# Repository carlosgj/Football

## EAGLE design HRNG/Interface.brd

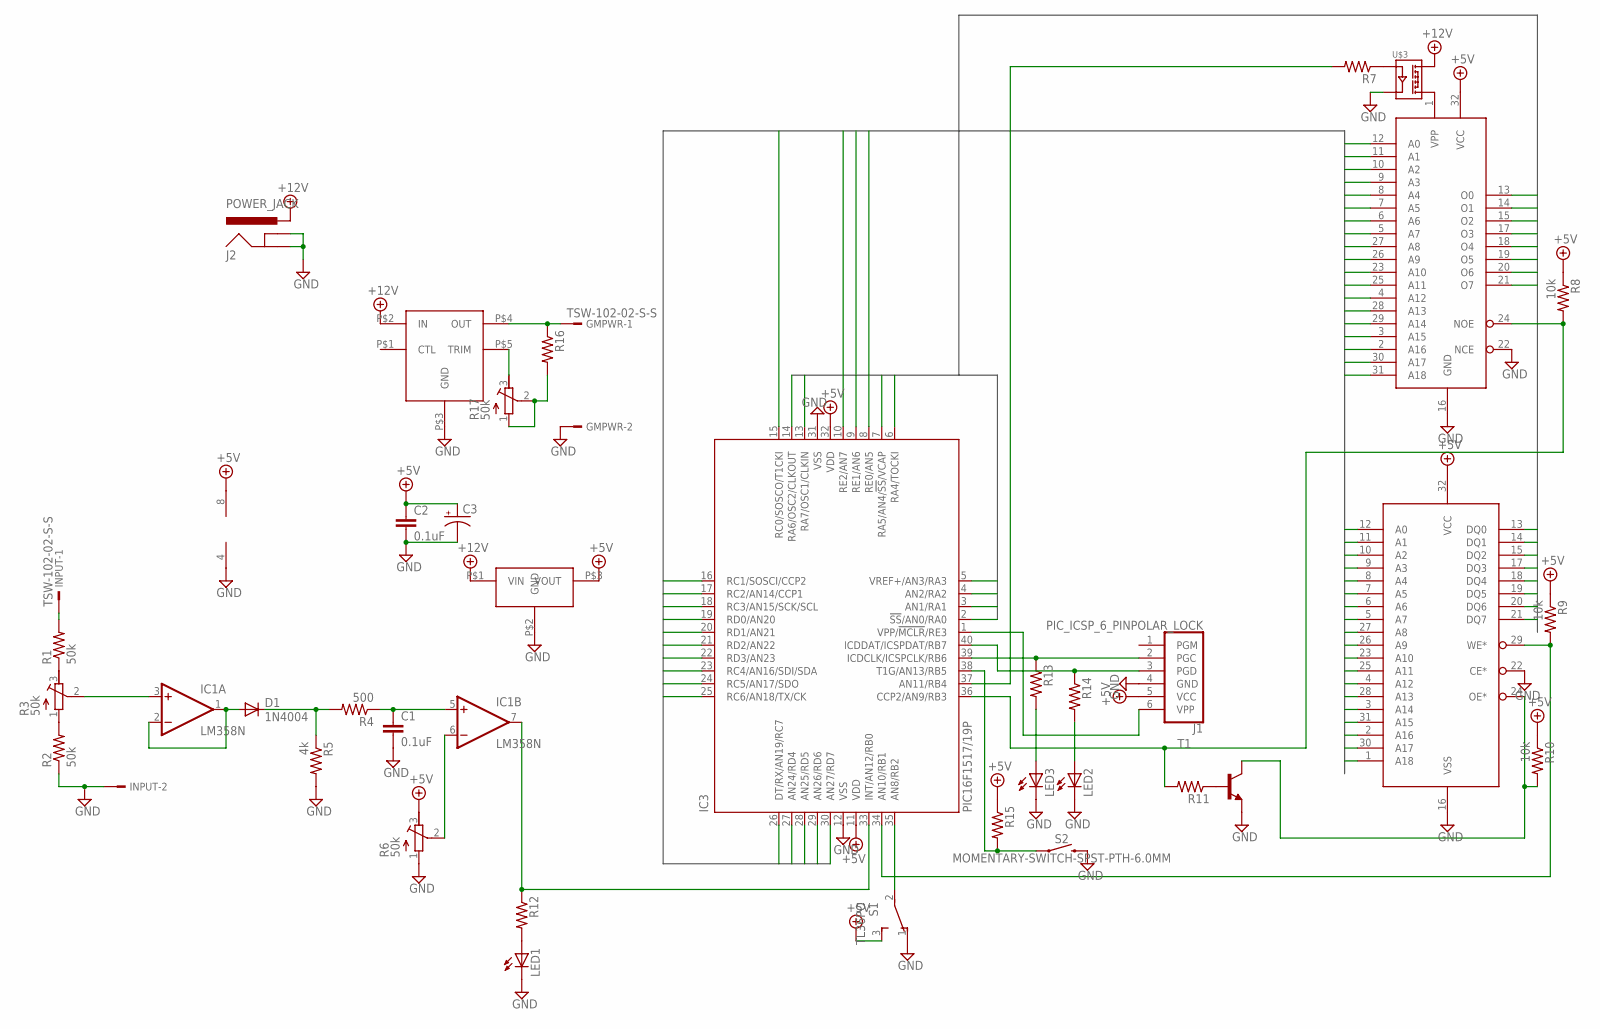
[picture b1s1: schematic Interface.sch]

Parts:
C1, C2: 0.1uF; C050-025X075
C3: CPOL-USE5-8.5; E5-8,5
D1: 1N4004; DO41-10
GMPWR: TSW-102-02-S-S
IC1: LM358N; DIL08
IC3: PIC16F1517/19P; DIL40
INPUT: TSW-102-02-S-S
J1: PIC_ICSP_6_PINPOLAR_LOCK; MOLEX-1X6_LOCK
J2: POWER_JACK; POWER_JACK_PTH
LED1, LED2, LED3: LED3MM
R1, R2: 50k; 0204V
R3, R6, R17: 50k; RTRIM3296W
R4: 500; 0204V
R5: 4k; 0204V
R7, R11, R12, R13, R14, R15, R16: R-US_0204/2V; 0204V
R8, R9, R10: 10k; 0204V
S1: TL36PO; TL3XPO
S2: MOMENTARY-SWITCH-SPST-PTH-6.0MM; TACTILE_SWITCH_PTH_6.0MM
T1: MPS2222A-NPN-TO92-CBE; TO92-CBE
U$1: AT27C040; DIL32
U$2: AS6C4008; DIL32
U$3: CPC1008N; SOP04
U$4: OKR-T/1.5-W12-C; SIP5
U$5: OKI-78SR-5/1.5-W36-C; SIP_PS

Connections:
+5V: C2.1, C3.+, IC1.8 (V+), IC3.11 (VDD), IC3.32 (VDD), J1.5 (VCC), R6.3 (E), R8.1, R9.1, R10.1, R15.1, S1.3 (S), U$1.32 (VCC), U$2.32 (VCC), U$5.P$3 (VOUT)
+12V: J2.PWR, U$3.4 (DC), U$4.P$2 (IN), U$5.P$1 (VIN)
A0: IC3.15 (RC0/SOSCO/T1CKI), U$1.12 (A0), U$2.12 (A0)
A1: IC3.16 (RC1/SOSCI/CCP2), U$1.11 (A1), U$2.11 (A1)
A2: IC3.17 (RC2/AN14/CCP1), U$1.10 (A2), U$2.10 (A2)
A3: IC3.18 (RC3/AN15/SCK/SCL), U$1.9 (A3), U$2.9 (A3)
A4: IC3.23 (RC4/AN16/SDI/SDA), U$1.8 (A4), U$2.8 (A4)
A5: IC3.24 (RC5/AN17/SDO), U$1.7 (A5), U$2.7 (A5)
A6: IC3.25 (RC6/AN18/TX/CK), U$1.6 (A6), U$2.6 (A6)
A7: IC3.26 (DT/RX/AN19/RC7), U$1.5 (A7), U$2.5 (A7)
A8: IC3.19 (RD0/AN20), U$1.27 (A8), U$2.27 (A8)
A9: IC3.20 (RD1/AN21), U$1.26 (A9), U$2.26 (A9)
A10: IC3.21 (RD2/AN22), U$1.23 (A10), U$2.23 (A10)
A11: IC3.22 (RD3/AN23), U$1.25 (A11), U$2.25 (A11)
A12: IC3.27 (AN24/RD4), U$1.4 (A12), U$2.4 (A12)
A13: IC3.28 (AN25/RD5), U$1.28 (A13), U$2.28 (A13)
A14: IC3.29 (AN26/RD6), U$1.29 (A14), U$2.3 (A14)
A15: IC3.30 (AN27/RD7), U$1.3 (A15), U$2.31 (A15)
A16: IC3.8 (RE0/AN5), U$1.2 (A16), U$2.2 (A16)
A17: IC3.9 (RE1/AN6), U$1.30 (A17), U$2.30 (A17)
A18: IC3.10 (RE2/AN7), U$1.31 (A18), U$2.1 (A18)
D0: IC3.2 (!SS!/AN0/RA0), U$1.13 (O0), U$2.13 (DQ0)
D1: IC3.3 (AN1/RA1), U$1.14 (O1), U$2.14 (DQ1)
D2: IC3.4 (AN2/RA2), U$1.15 (O2), U$2.15 (DQ2)
D3: IC3.5 (VREF+/AN3/RA3), U$1.17 (O3), U$2.17 (DQ3)
D4: IC3.6 (RA4/TOCKI), U$1.18 (O4), U$2.18 (DQ4)
D5: IC3.7 (RA5/AN4/!SS!/VCAP), U$1.19 (O5), U$2.19 (DQ5)
D6: IC3.14 (RA6/OSC2/CLKOUT), U$1.20 (O6), U$2.20 (DQ6)
D7: IC3.13 (RA7/OSC1/CLKIN), U$1.21 (O7), U$2.21 (DQ7)
GND: C1.2, C2.2, C3.-, GMPWR.2, IC1.4 (V-), IC3.12 (VSS), IC3.31 (VSS), INPUT.2, J1.4 (GND), J2.GND, J2.GNDBREAK, LED1.K (C), LED2.K (C), LED3.K (C), R2.1, R5.2, R6.1 (A), S1.1 (O), S2.3 (2), T1.E, U$1.16 (GND), U$1.22 (NCE), U$2.16 (VSS), U$2.22 (CE*), U$3.3 (IN-), U$4.P$3 (GND), U$5.P$2 (GND)
unnamed: R1.1, R3.3 (E)
unnamed: R2.2, R3.1 (A)
unnamed: IC1.6 (-IN), R6.2 (S)
unnamed: INPUT.1, R1.2
unnamed: D1.A, IC1.1 (OUT), IC1.2 (-IN)
unnamed: IC1.3 (+IN), R3.2 (S)
unnamed: D1.C, R4.2, R5.1
unnamed: C1.1, IC1.5 (+IN), R4.1
unnamed: IC3.39 (ICDCLK/ICSPCLK/RB6), J1.2 (PGC), R13.1
unnamed: IC3.40 (ICDDAT/ICSPDAT/RB7), J1.3 (PGD), R14.1
unnamed: IC3.34 (AN10/RB1), R9.2, U$2.29 (WE*)
unnamed: R11.1, T1.B
unnamed: IC3.36 (CCP2/AN9/RB3), R8.2, R11.2, U$1.24 (NOE)
unnamed: IC1.7 (OUT), IC3.33 (INT/AN12/RB0), R12.1
unnamed: IC3.1 (VPP/!MCLR!/RE3), J1.6 (VPP)
unnamed: U$1.1 (VPP), U$3.6 (DC)
unnamed: R7.1, U$3.1 (IN+)
unnamed: IC3.37 (AN11/RB4), R7.2
unnamed: R10.2, T1.C, U$2.24 (OE*)
unnamed: LED1.A, R12.2
unnamed: IC3.35 (AN8/RB2), S1.2
unnamed: LED2.A, R14.2
unnamed: LED3.A, R13.2
unnamed: IC3.38 (T1G/AN13/RB5), R15.2, S2.1
unnamed: GMPWR.1, R16.1, U$4.P$4 (OUT)
unnamed: R17.3 (E), U$4.P$5 (TRIM)
unnamed: R16.2, R17.1 (A), R17.2 (S)

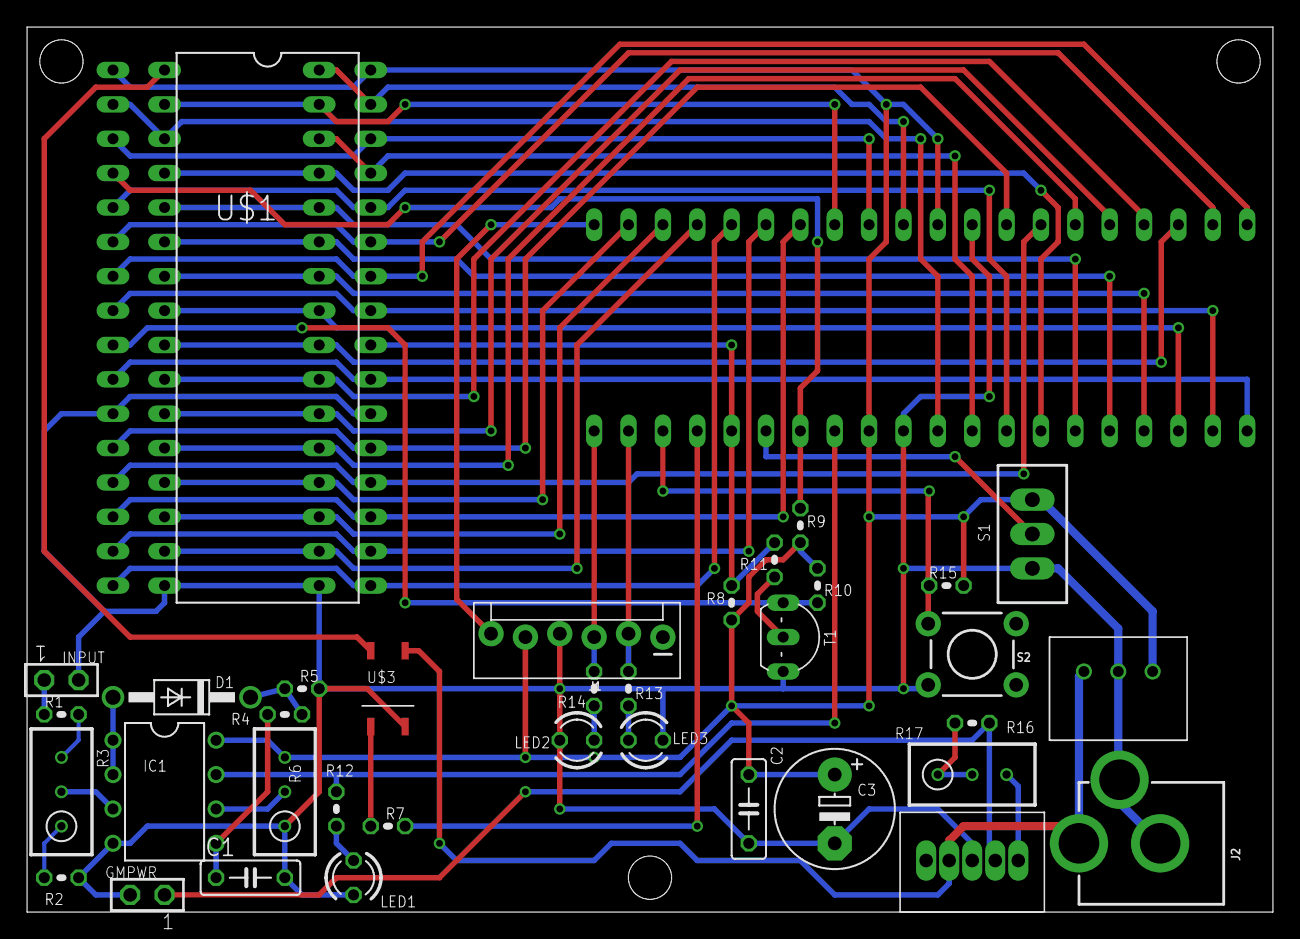
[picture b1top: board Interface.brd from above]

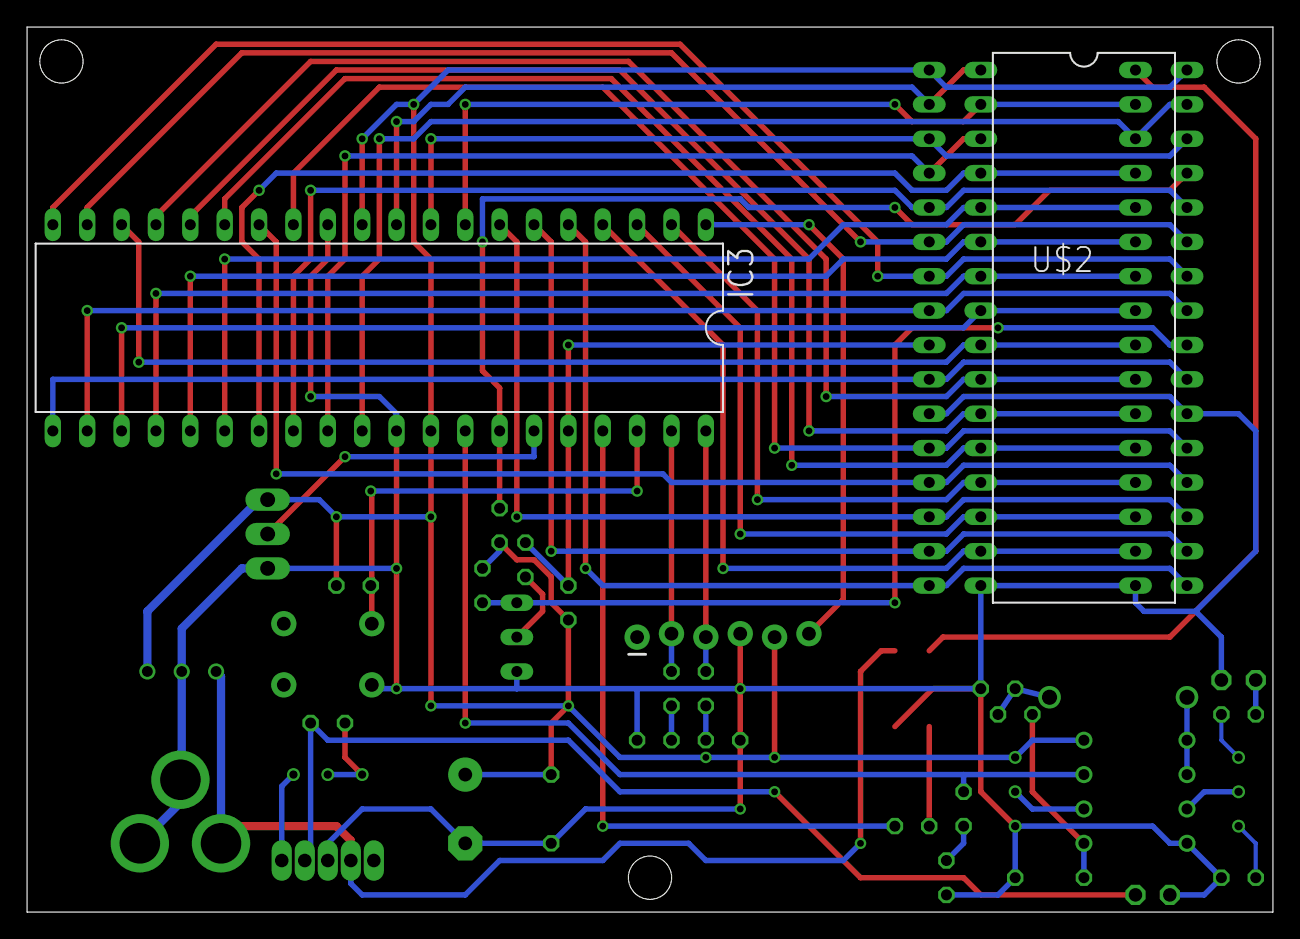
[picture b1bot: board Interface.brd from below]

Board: 2 copper layers, 92.1 x 65.4 mm, 38 parts (2 on the bottom side), 57 nets.

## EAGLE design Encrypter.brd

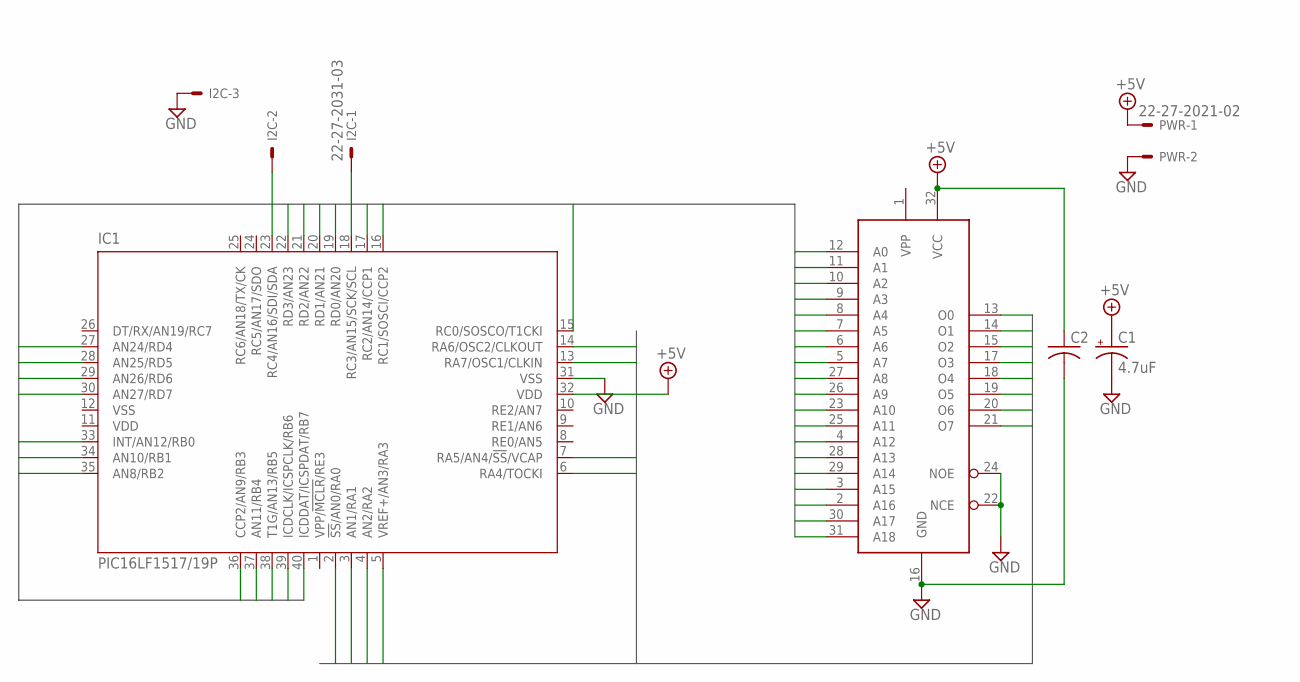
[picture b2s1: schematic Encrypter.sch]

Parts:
C1: 4.7uF; E3,5-10
C2: C-US050-025X075; C050-025X075
I2C: 22-27-2031-03; 6410-03
IC1: PIC16LF1517/19P; DIL40
PWR: 22-27-2021-02; 6410-02
U$1: AT27C040; DIL32

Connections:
+5V: C1.+, C2.1, IC1.32 (VDD), PWR.1, U$1.32 (VCC)
A0: IC1.33 (INT/AN12/RB0), U$1.12 (A0)
A1: IC1.34 (AN10/RB1), U$1.11 (A1)
A2: IC1.35 (AN8/RB2), U$1.10 (A2)
A3: IC1.36 (CCP2/AN9/RB3), U$1.9 (A3)
A4: IC1.37 (AN11/RB4), U$1.8 (A4)
A5: IC1.38 (T1G/AN13/RB5), U$1.7 (A5)
A6: IC1.39 (ICDCLK/ICSPCLK/RB6), U$1.6 (A6)
A7: IC1.40 (ICDDAT/ICSPDAT/RB7), U$1.5 (A7)
A8: IC1.15 (RC0/SOSCO/T1CKI), U$1.27 (A8)
A9: IC1.16 (RC1/SOSCI/CCP2), U$1.26 (A9)
A10: IC1.17 (RC2/AN14/CCP1), U$1.23 (A10)
A11: IC1.19 (RD0/AN20), U$1.25 (A11)
A12: IC1.20 (RD1/AN21), U$1.4 (A12)
A13: IC1.21 (RD2/AN22), U$1.28 (A13)
A14: IC1.22 (RD3/AN23), U$1.29 (A14)
A15: IC1.27 (AN24/RD4), U$1.3 (A15)
A16: IC1.28 (AN25/RD5), U$1.2 (A16)
A17: IC1.29 (AN26/RD6), U$1.30 (A17)
A18: IC1.30 (AN27/RD7), U$1.31 (A18)
GND: C1.-, C2.2, I2C.3, IC1.31 (VSS), PWR.2, U$1.16 (GND), U$1.22 (NCE), U$1.24 (NOE)
unnamed: I2C.1, IC1.18 (RC3/AN15/SCK/SCL)
unnamed: I2C.2, IC1.23 (RC4/AN16/SDI/SDA)
O0: IC1.2 (!SS!/AN0/RA0), U$1.13 (O0)
O1: IC1.3 (AN1/RA1), U$1.14 (O1)
O2: IC1.4 (AN2/RA2), U$1.15 (O2)
O3: IC1.5 (VREF+/AN3/RA3), U$1.17 (O3)
O4: IC1.6 (RA4/TOCKI), U$1.18 (O4)
O5: IC1.7 (RA5/AN4/!SS!/VCAP), U$1.19 (O5)
O6: IC1.14 (RA6/OSC2/CLKOUT), U$1.20 (O6)
O7: IC1.13 (RA7/OSC1/CLKIN), U$1.21 (O7)
VDD: IC1.11 (VDD)
VSS: IC1.12 (VSS)

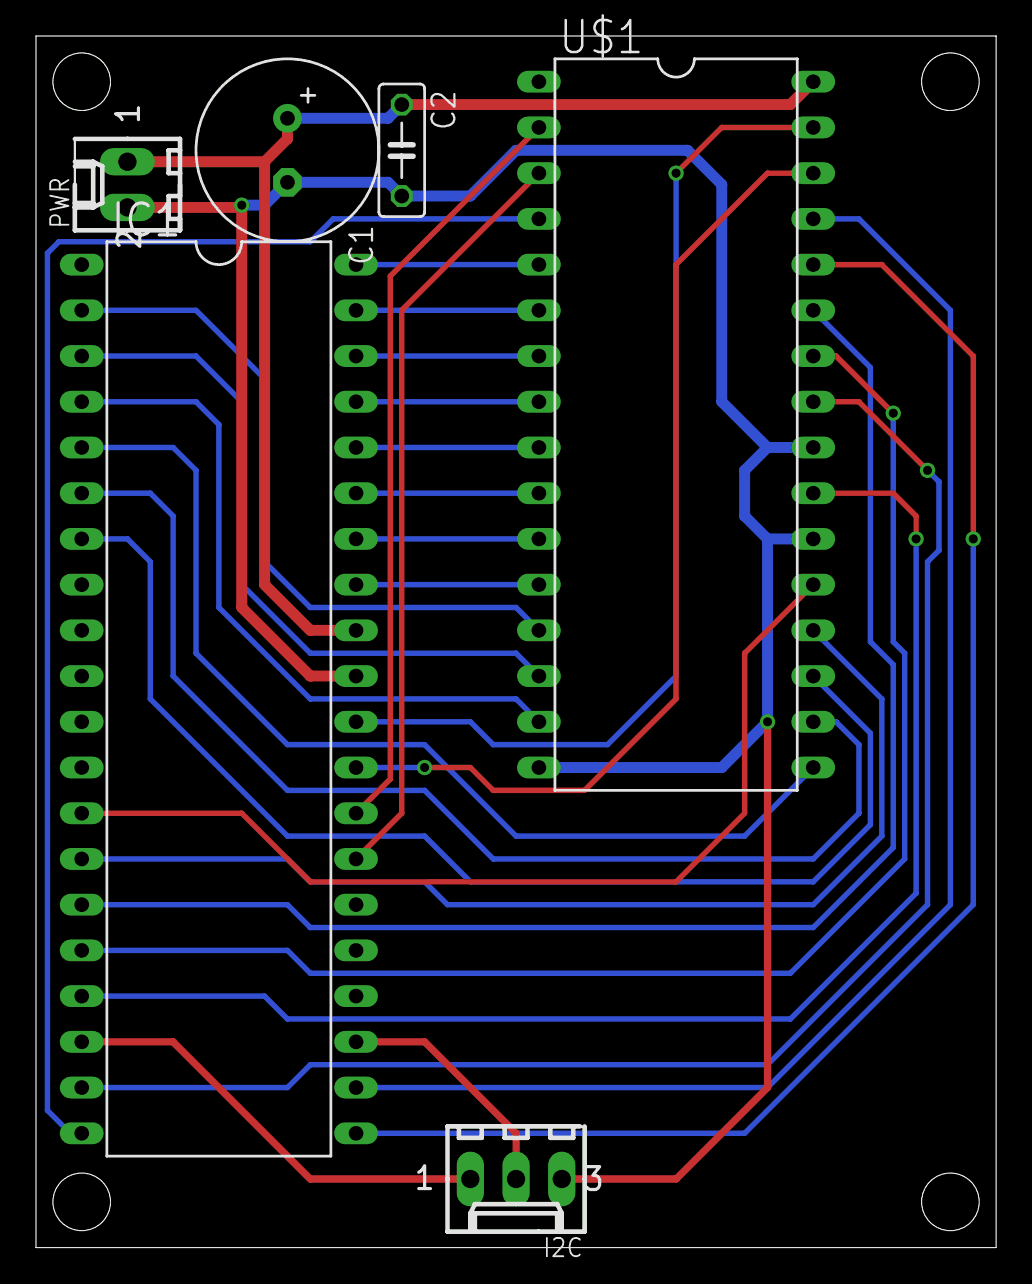
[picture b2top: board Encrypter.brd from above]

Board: 2 copper layers, 53.3 x 67.3 mm, 6 parts (0 on the bottom side), 31 nets.

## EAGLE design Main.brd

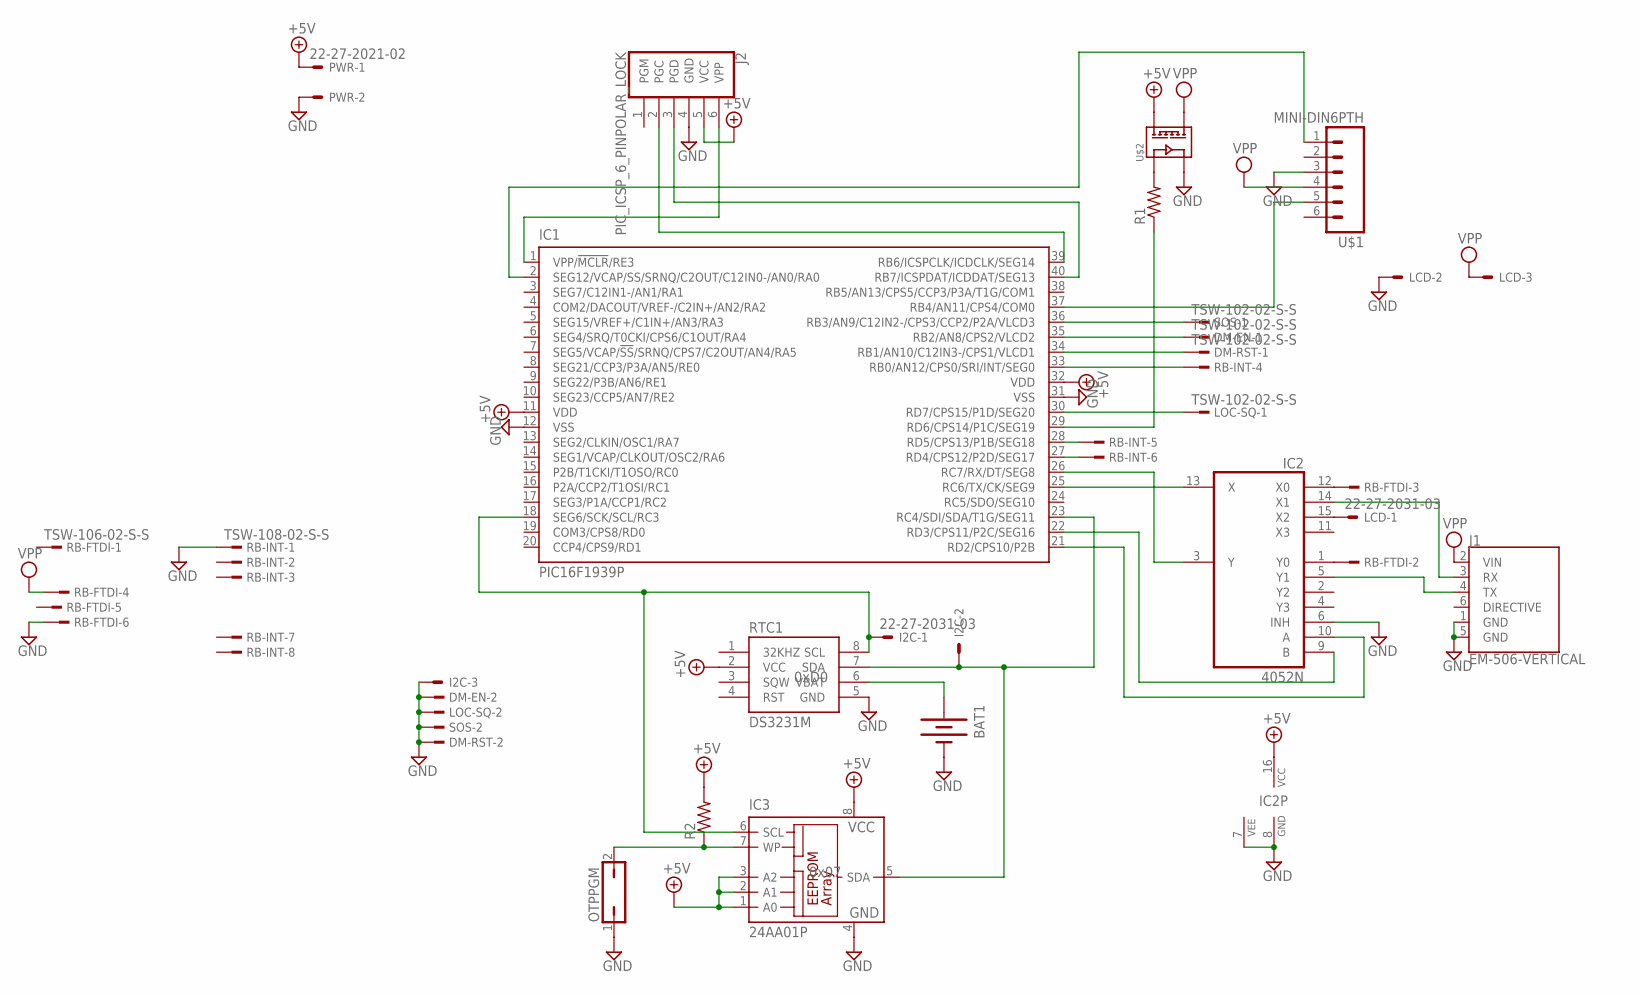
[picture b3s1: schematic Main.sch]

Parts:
BAT1: BATTERY12PTH; BATTCON_12MM_PTH
DM-EN: TSW-102-02-S-S
DM-RST: TSW-102-02-S-S
I2C: 22-27-2031-03; 6410-03
IC1: PIC16F1939P; DIL40
IC2: 4052N; DIL16
IC3: 24AA01P; DIL8
J1: EM-506-VERTICAL; EM406
J2: PIC_ICSP_6_PINPOLAR_LOCK; MOLEX-1X6_LOCK
LCD: 22-27-2031-03; 6410-03
LOC-SQ: TSW-102-02-S-S
OTPPGM: JP1Q; JP1
PWR: 22-27-2021-02; 6410-02
R1, R2: R-US_0204/2V; 0204V
RB-FTDI: TSW-106-02-S-S
RB-INT: TSW-108-02-S-S
RTC1: DS3231M; SOIC8
SOS: TSW-102-02-S-S
U$1: MINI-DIN6PTH; MINI-DIN6
U$2: CPC1008N; SOP04

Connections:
+5V: IC1.11 (VDD), IC1.32 (VDD), IC2.16 (VCC), IC3.1 (A0), IC3.2 (A1), IC3.3 (A2), IC3.8 (VCC), J2.5 (VCC), PWR.1, R2.2, RTC1.2 (VCC), U$2.4 (DC)
GND: BAT1.GND (-), DM-EN.2, DM-RST.2, I2C.3, IC1.12 (VSS), IC1.31 (VSS), IC2.6 (INH), IC2.7 (VEE), IC2.8 (GND), IC3.4 (GND), J1.1 (GND), J1.5 (GND), J2.4 (GND), LCD.2, LOC-SQ.2, OTPPGM.1, PWR.2, RB-FTDI.6, RB-INT.1, RTC1.5 (GND), SOS.2, U$1.3, U$2.3 (IN-)
unnamed: IC1.26 (RC7/RX/DT/SEG8), IC2.3 (Y)
unnamed: IC1.25 (RC6/TX/CK/SEG9), IC2.13 (X)
unnamed: I2C.1, IC1.18 (SEG6/SCK/SCL/RC3), IC3.6 (SCL), RTC1.8 (SCL)
unnamed: I2C.2, IC1.23 (RC4/SDI/SDA/T1G/SEG11), IC3.5 (SDA), RTC1.7 (SDA)
unnamed: IC1.30 (RD7/CPS15/P1D/SEG20), LOC-SQ.1
unnamed: BAT1.VCC@1 (+), RTC1.6 (VBAT)
unnamed: IC2.12 (X0), RB-FTDI.3
unnamed: IC2.1 (Y0), RB-FTDI.2
unnamed: IC2.14 (X1), J1.3 (RX)
unnamed: IC2.5 (Y1), J1.4 (TX)
unnamed: IC1.22 (RD3/CPS11/P2C/SEG16), IC2.9 (B)
unnamed: IC2.15 (X2), LCD.1
unnamed: IC1.21 (RD2/CPS10/P2B), IC2.10 (A)
unnamed: IC1.37 (RB4/AN11/CPS4/COM0), U$1.5
unnamed: IC1.39 (RB6/ICSPCLK/ICDCLK/SEG14), J2.2 (PGC)
unnamed: IC1.40 (RB7/ICSPDAT/ICDDAT/SEG13), J2.3 (PGD)
unnamed: R1.2, U$2.1 (IN+)
unnamed: IC1.33 (RB0/AN12/CPS0/SRI/INT/SEG0), RB-INT.4
unnamed: IC1.28 (RD5/CPS13/P1B/SEG18), RB-INT.5
unnamed: IC1.27 (RD4/CPS12/P2D/SEG17), RB-INT.6
unnamed: DM-RST.1, IC1.34 (RB1/AN10/C12IN3-/CPS1/VLCD1)
unnamed: DM-EN.1, IC1.35 (RB2/AN8/CPS2/VLCD2)
unnamed: IC1.36 (RB3/AN9/C12IN2-/CPS3/CCP2/P2A/VLCD3), SOS.1
unnamed: IC1.2 (SEG12/VCAP/SS/SRNQ/C2OUT/C12IN0-/AN0/RA0), U$1.1
unnamed: IC1.29 (RD6/CPS14/P1C/SEG19), R1.1
unnamed: IC3.7 (WP), OTPPGM.2, R2.1
unnamed: IC1.1 (VPP/!MCLR!/RE3), J2.6 (VPP)
VPP: J1.2 (VIN), LCD.3, RB-FTDI.4, U$1.4, U$2.6 (DC)

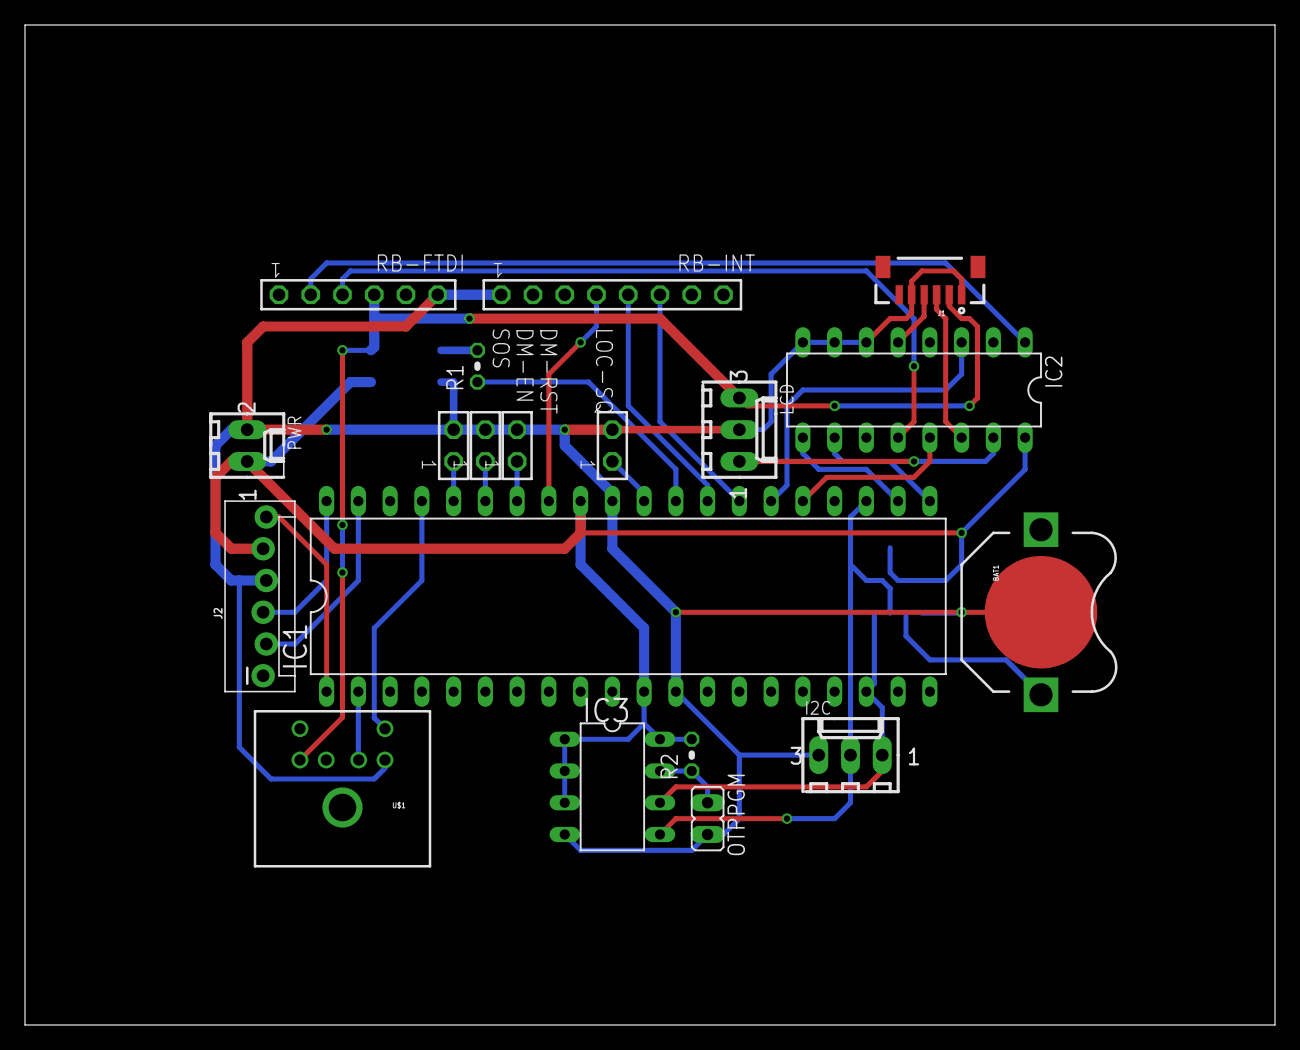
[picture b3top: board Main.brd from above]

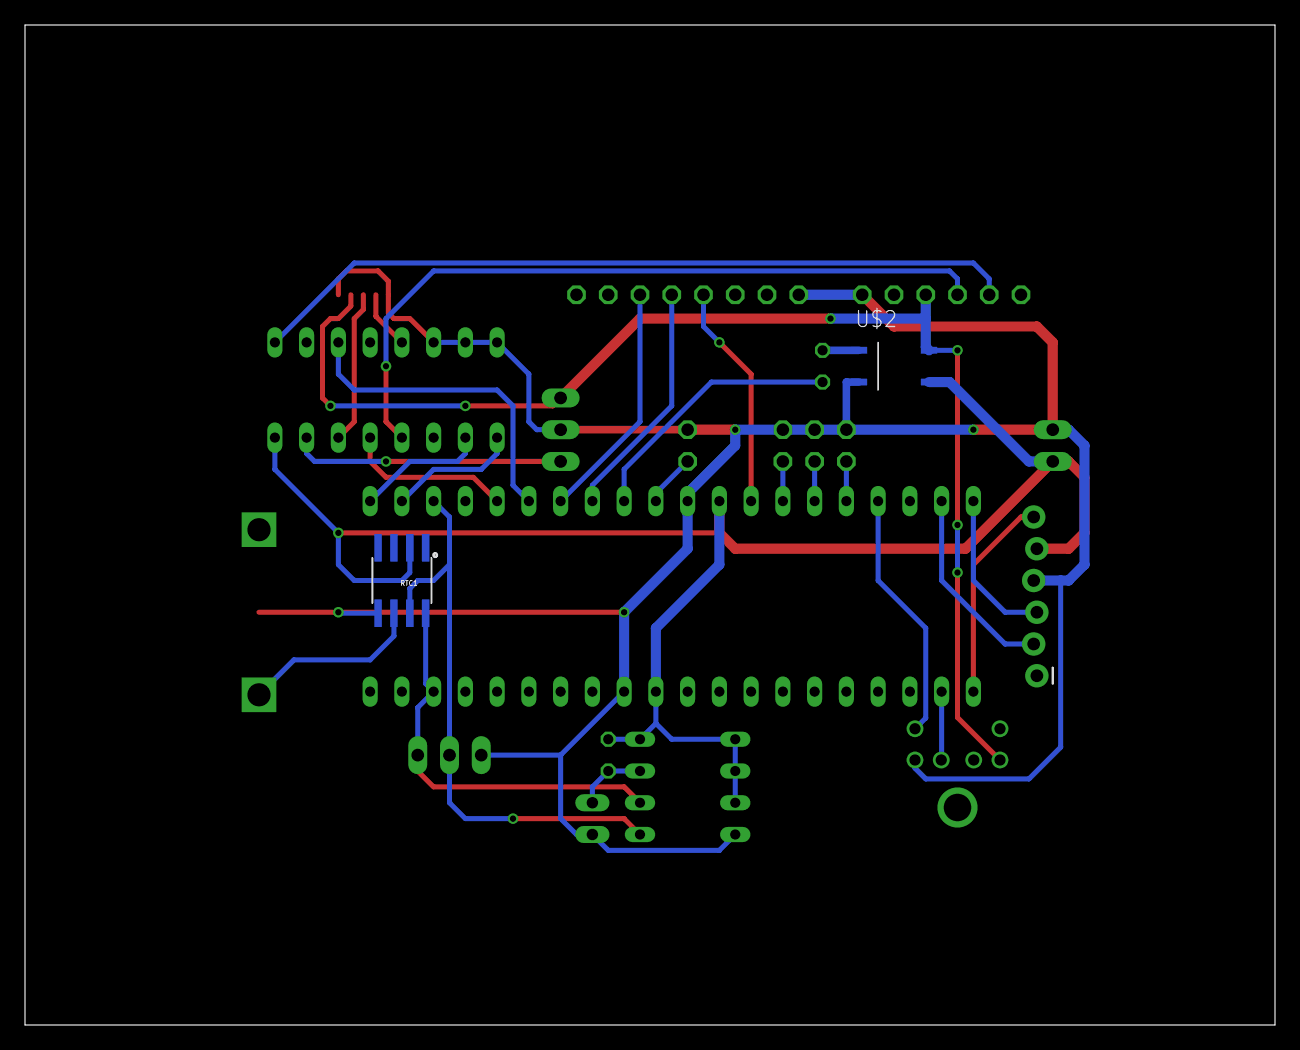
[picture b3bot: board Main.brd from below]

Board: 2 copper layers, 100.0 x 80.0 mm, 21 parts (2 on the bottom side), 30 nets.

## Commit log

2016-12-18 HRNG
2016-12-19 Encrypter work
2016-12-29 Board updates
2021-05-05 Initial code
2021-05-05 Project documentation
2021-05-06 More code structure
2021-05-10 CAD work
2021-05-10 Code work
2021-05-10 Started hardware testing - Basic sleep cycle works - ms timer works - Debug serial TX works
2021-06-18 Enabling IOC for UI switch
2021-06-18 Working on GPS message parsing
2021-06-21 Work on GPS parsing
2021-06-21 GPS parsing mostly works

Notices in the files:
parts and their libraries:
SparkFun-Connectors: Licensing: Creative Commons ShareAlike 4.0 International - https://creativecommons.org/licenses/by-sa/4.0
